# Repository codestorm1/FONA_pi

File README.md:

# FONA_pi
KiCad design for FONA + raspberry pi

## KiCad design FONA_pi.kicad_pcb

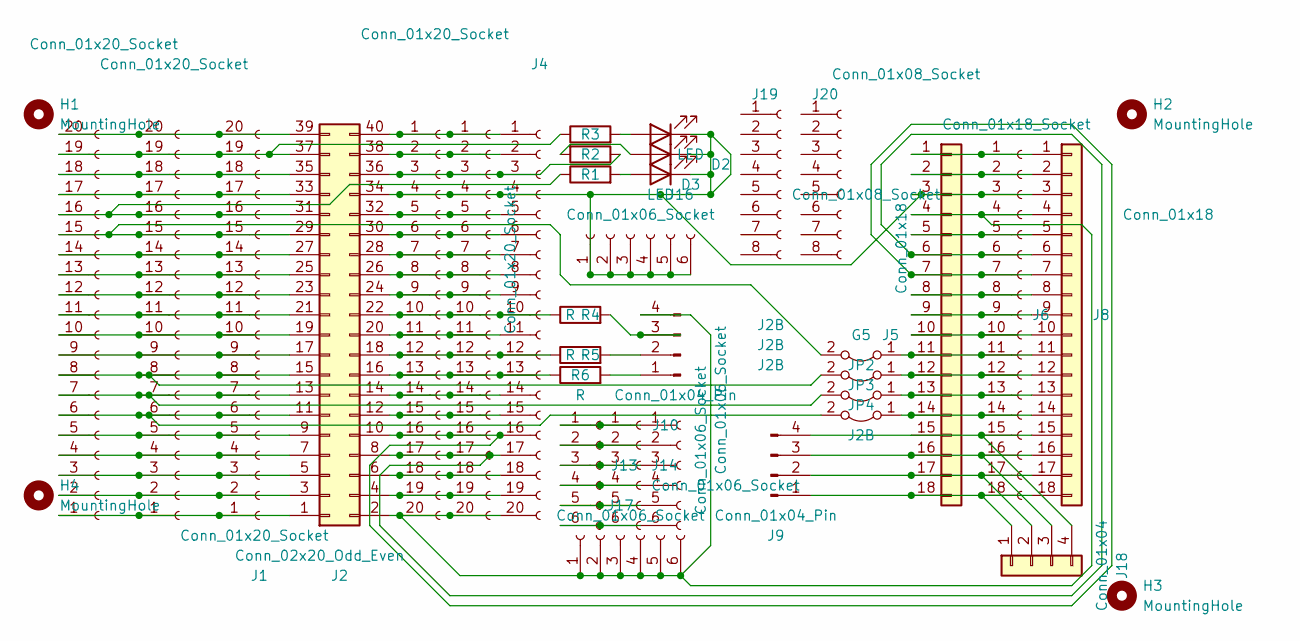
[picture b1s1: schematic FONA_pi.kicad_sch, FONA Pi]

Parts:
D1, D2, D3: LED; LED_D3.0mm
G5: J2B; SolderJumper-2_P1.3mm_Bridged_RoundedPad1.0x1.5mm
H1, H2, H3, H4: MountingHole; MountingHole_2.5mm
J1, J3, J11, J12: Conn_01x20_Socket; PinSocket_1x20_P2.54mm_Vertical
J2: Conn_02x20_Odd_Even; PinSocket_2x20_P2.54mm_Vertical
J4, J7: Conn_01x20_Socket; PinHeader_1x20_P2.54mm_Vertical
J5, J8: Conn_01x18; PinSocket_1x18_P2.54mm_Vertical
J6: Conn_01x18_Socket; PinSocket_1x18_P2.54mm_Vertical
J9, J10: Conn_01x04_Pin; JST_XH_B4B-XH-A_1x04_P2.50mm_Vertical
J13, J14, J15, J16, J17: Conn_01x06_Socket; PinSocket_1x06_P2.54mm_Vertical
J18: Conn_01x04; Wago_734-134_1x04_P3.50mm_Vertical
J19, J20: Conn_01x08_Socket; PinSocket_1x08_P2.54mm_Vertical
JP2, JP3, JP4: J2B; SolderJumper-2_P1.3mm_Bridged_RoundedPad1.0x1.5mm
R1, R2, R3, R4, R5, R6: R; R_Axial_DIN0207_L6.3mm_D2.5mm_P7.62mm_Horizontal

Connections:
unnamed: D1.2 (A), R3.2
unnamed: D1.1 (K), D2.1 (K), D3.1 (K), J2.34, J3.4, J4.4, J5.3, J6.3, J7.4, J8.3, J16.1, J16.2, J16.3, J16.4, J16.5, J16.6
unnamed: D2.2 (A), R2.2
unnamed: D3.2 (A), R1.2
unnamed: G5.1 (A), J5.11, J6.11, J8.11
unnamed: G5.2 (B), J1.15, J2.29, J11.15, J12.15
unnamed: J1.1, J2.1, J11.1, J12.1
unnamed: J1.2, J2.3, J11.2, J12.2
unnamed: J1.3, J2.5, J11.3, J12.3
unnamed: J1.4, J2.7, J11.4, J12.4
unnamed: J1.5, J2.9, J11.5, J12.5
unnamed: J1.6, J2.11, J11.6, J12.6, JP4.2 (B)
unnamed: J1.7, J2.13, J11.7, J12.7, JP3.2 (B)
unnamed: J1.8, J2.15, J11.8, J12.8, JP2.2 (B)
unnamed: J1.9, J2.17, J11.9, J12.9
unnamed: J1.10, J2.19, J11.10, J12.10
unnamed: J1.11, J2.21, J11.11, J12.11
unnamed: J1.12, J2.23, J11.12, J12.12
unnamed: J1.13, J2.25, J11.13, J12.13
unnamed: J1.14, J2.27, J11.14, J12.14
unnamed: J1.16, J2.31, J11.16, J12.16, R1.1
unnamed: J1.17, J2.33, J11.17, J12.17
unnamed: J1.18, J2.35, J11.18, J12.18
unnamed: J1.19, J2.37, J11.19, J12.19, R3.1
unnamed: J1.20, J2.39, J11.20, J12.20
unnamed: J2.4, J3.19, J4.19, J7.19
unnamed: J2.6, J3.18, J4.18, J7.18
unnamed: J2.8, J3.17, J4.17, J5.6, J6.6, J7.17, J8.6
unnamed: J2.10, J3.16, J4.16, J5.7, J6.7, J7.16, J8.7
unnamed: J2.12, J3.15, J4.15, J7.15
unnamed: J2.14, J3.14, J4.14, J7.14
unnamed: J2.16, J3.13, J4.13, J7.13, R6.1
unnamed: J2.18, J3.12, J4.12, J7.12, R5.1
unnamed: J2.20, J3.11, J4.11, J7.11
unnamed: J2.22, J3.10, J4.10, J7.10, R4.1
unnamed: J2.24, J3.9, J4.9, J7.9
unnamed: J2.26, J3.8, J4.8, J7.8
unnamed: J2.28, J3.7, J4.7, J7.7
unnamed: J2.30, J3.6, J4.6, J7.6
unnamed: J2.32, J3.5, J4.5, J7.5
unnamed: J2.36, J3.3, J4.3, J7.3, R2.1
unnamed: J2.38, J3.2, J4.2, J7.2
unnamed: J2.40, J3.1, J4.1, J7.1
unnamed: J5.1, J6.1, J8.1
unnamed: J5.2, J6.2, J8.2
unnamed: J5.5, J6.5, J8.5
unnamed: J5.8, J6.8, J8.8
unnamed: J5.9, J6.9, J8.9
unnamed: J5.10, J6.10, J8.10
unnamed: J5.12, J6.12, J8.12, JP2.1 (A)
unnamed: J5.13, J6.13, J8.13, JP3.1 (A)
unnamed: J5.14, J6.14, J8.14, JP4.1 (A)
unnamed: J10.1, R6.2
unnamed: J10.2, R5.2
unnamed: J10.3, R4.2
unnamed: J2.2, J3.20, J4.20, J5.4, J6.4, J7.20, J8.4, J10.4, J17.1, J17.2, J17.3, J17.4, J17.5, J17.6
unnamed: J13.1, J14.1, J15.1
unnamed: J13.2, J14.2, J15.2
unnamed: J13.3, J14.3, J15.3
unnamed: J13.4, J14.4, J15.4
unnamed: J13.5, J14.5, J15.5
unnamed: J13.6, J14.6, J15.6
unnamed: J5.18, J6.18, J8.18, J9.1, J18.1
unnamed: J5.17, J6.17, J8.17, J9.2, J18.2
unnamed: J5.16, J6.16, J8.16, J9.3, J18.3
unnamed: J5.15, J6.15, J8.15, J9.4, J18.4

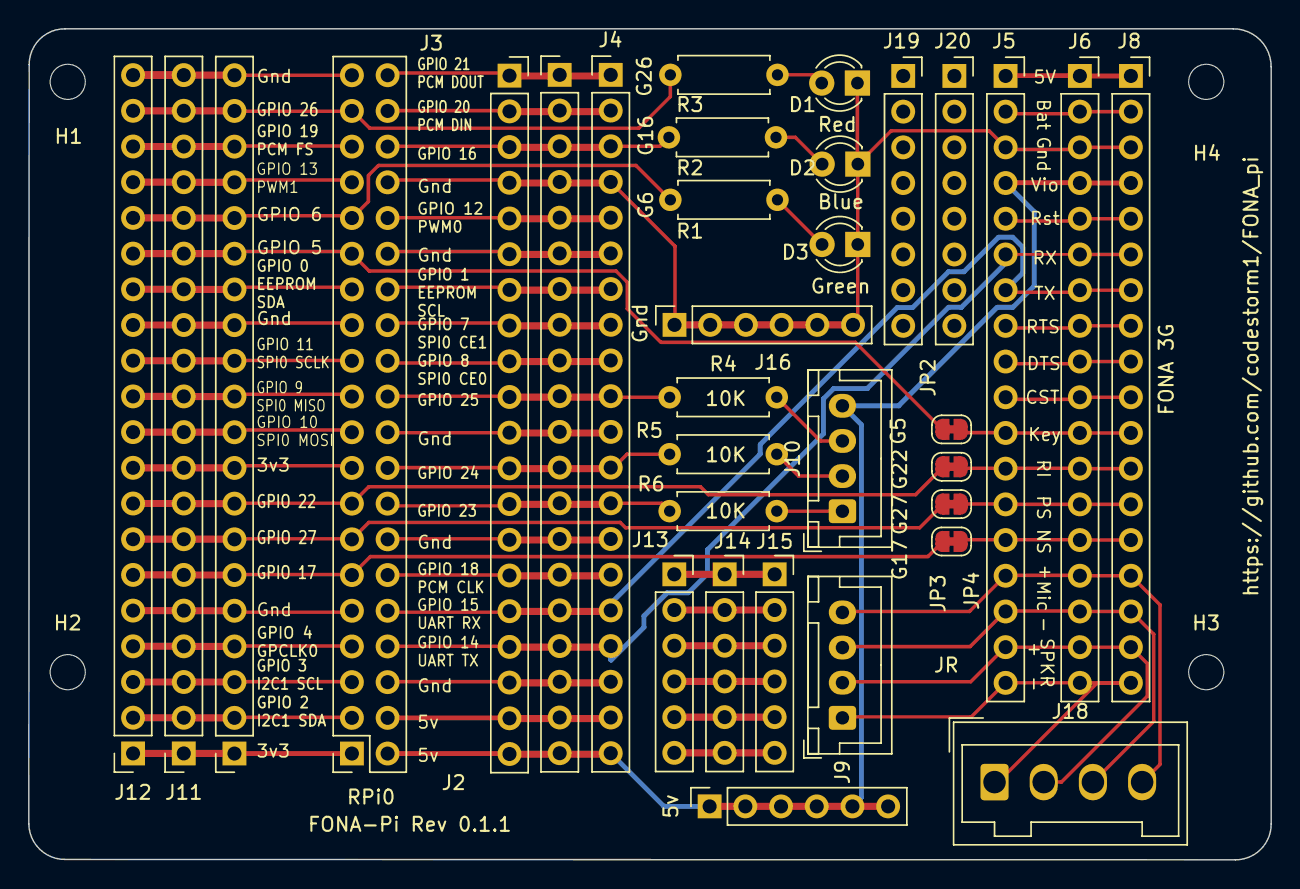
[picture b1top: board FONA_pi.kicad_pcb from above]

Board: 2 copper layers, 88.4 x 59.1 mm, 37 parts (0 on the bottom side), 66 nets.

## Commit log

2023-08-06 kicad project changes
2023-08-10 Added a 2x20
2023-08-13 Added some 1x20 to schematic
2023-08-16 connections for pi and fona
2023-09-03 Moving all square pins to top
2023-09-10 Flipped all the sockets so the pins are all aligned the same with square holes at the top, sch and pcb
2023-09-11 Got rid of the headers in 3D viewer. Cleaned up pin headers. Using 40-pin Rpi header
2023-09-11 Added more rows of holes to connect to Pi
2023-09-12 Rounded corners on edge cuts
2023-09-12 some minor change?
2023-09-13 about to try making a hole in the mask layer
2023-09-16 first filled polygons on mask level, letting copper sow through
2023-09-17 flipped RPi orientation on schematic. Added three 3mm LEDs with resistors on sch and pcb. Wired up with traces
2023-09-17 Hooked up JST-XH connectors, resistors
2023-09-17 Made space near FONA for silkscreen text
2023-09-17 Flipped RPi pins. Added silkscreen labels for pins. Connected wires and tracks
2023-09-18 lots of pin and trace cleanup
2023-09-18 Corrected a lot of Rpi0 pin names
2023-09-20 Added two more rails for the left side of the Rpi0
2023-09-23 tweaks after running DRC
2023-09-23 Made a bunch of warning fixes. Silkscreen lettering, etc
2023-09-23 Added fat tracks to the Pi prototyping area
2023-09-23 Added rectangles in mask. Exposes tracks as desired, but tons of errors
2023-09-23 Added isolated proto area
2023-09-23 Added power and ground rails
2023-09-25 Added solder jumpers, ran them to GPIO pins. Connected FONA pins to Pi, UART RX/TX, RI, NS, PS, etc to various GPIOs
2023-09-25 Masked any traces that were going in between Pi pin solder pads
2023-09-26 little fixes, tracks, etc.
2023-09-26 Changed GPIO pins, so that no multi-purpose (UART/SPI/I2C) pins are used by default by the FONA, LEDs or switch connector, to keep them free for those uses
2023-09-26 Covered up some track with mask that were exposed after changing pin connections
2023-09-28 Made the board smaller and used less rounded corners. Added mounting holes with pads.
2023-09-29 aligned edge cuts
2023-09-29 re-saved files
2023-09-29 fiddling with mounting hole positions
2023-09-29 Moved text inside edge cuts
2023-09-30 Added text for RPi and FONA 3G, aligned text for RPi pins. Masked EEPROM SDA row
2023-09-30 shifted text around
2023-09-30 Had to reposition a lot after pulling in from schematic
2023-09-30 Fixed DRC violations
2023-09-30 last commit didn't have some saved files that are in this commit
2023-10-01 Rearranged jumper pads and tracks
2023-10-01 Moved TX RX and +5V tracks to B.Cu
2023-10-01 Re-routed tracks for the solder pads to more direct route to RPi
2023-10-01 Had to place components from the schematic that I had already been placed (?). Update PCB is fine from this point
2023-10-01 Need to fix solder pad positioning again
2023-10-01 Placed footprints again.
2023-10-01 Fixed DRC errors
2023-10-01 Labeled some pin connections
2023-10-01 Adjusted text positions
2023-10-01 Added mounting holes (again)
2023-10-01 Changed some B.Cu tracks
2023-10-02 Removed mounting hole refs
2023-10-02 Fixed masking on EEPROM SCL And GND rail
2023-10-02 Made 5v and Gnd rails thicker. Need to fix 5V tracks
2023-10-02 Thickened the 5v tracks.
2023-10-02 Removed spots for capacitors
2023-10-02 Aligned some text
2023-10-02 Generated gerber files
2023-10-02 Added connector pins J19 and J20, to associate with connectors in pcb. Lost mounting holes
2023-10-02 Reverted some changes. Needs to update from schematic and see what breaks
2023-10-02 Re-did some tracks after getting errors from updating from sch
2023-10-02 Loosely positioned mounting holes
2023-10-02 Positioned mounting holes
2023-10-05 Flipped a backwards resistor. Added labels for LED colors, switch resistors
2023-10-05 Changed which wire of wire harness is used for power. Now using the first wire from the top, which is a red wire on the harness, so that 5v power will be on the red wire
2023-10-05 Created new gerber files
2023-10-08 Not sure what was in this update
2023-10-17 Grounded FONA to Pi
2023-10-17 Changed rev to 0.1.1
